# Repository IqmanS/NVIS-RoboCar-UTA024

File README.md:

## NVIS 3302ARD Robocar (UTA024: Engineering Design Project - II)
<p>
Read More about it: https://medium.com/@iqmans/creating-a-line-following-robocar-with-obstacle-detection-668964e0befc 
</p>
<p>
This is a Group Project and it is offered jointly by the department of Electronics Engineering and the department of Computer Engineering to the 2nd year students of all branches of Thapar Institute of Engineering and Technology.
</p>
<div align="center">
 
</div>

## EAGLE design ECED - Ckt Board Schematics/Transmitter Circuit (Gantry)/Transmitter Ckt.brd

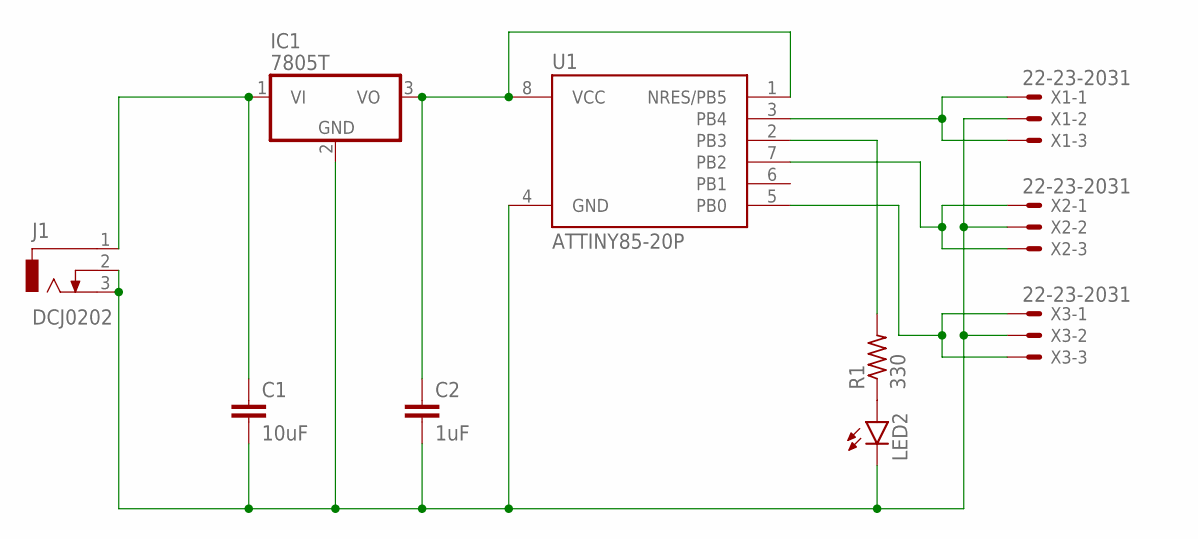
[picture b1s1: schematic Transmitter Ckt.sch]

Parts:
C1: 10uF; C0603
C2: 1uF; C0603
IC1: 7805T; TO220H
J1: DCJ0202
LED2: LED3MM
R1: 330; R0603
U1: ATTINY85-20P; PDIP08_300MIL
X1, X2, X3: 22-23-2031

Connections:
unnamed: LED2.A, R1.1
unnamed: C1.1, IC1.1 (VI), J1.1
unnamed: U1.3 (PB4), X1.1, X1.3
unnamed: C2.1, IC1.3 (VO), U1.1 (NRES/PB5), U1.8 (VCC)
unnamed: R1.2, U1.2 (PB3)
unnamed: U1.7 (PB2), X2.1, X2.3
unnamed: U1.5 (PB0), X3.1, X3.3
unnamed: C1.2, C2.2, IC1.2 (GND), J1.2, J1.3, LED2.K (C), U1.4 (GND), X1.2, X2.2, X3.2

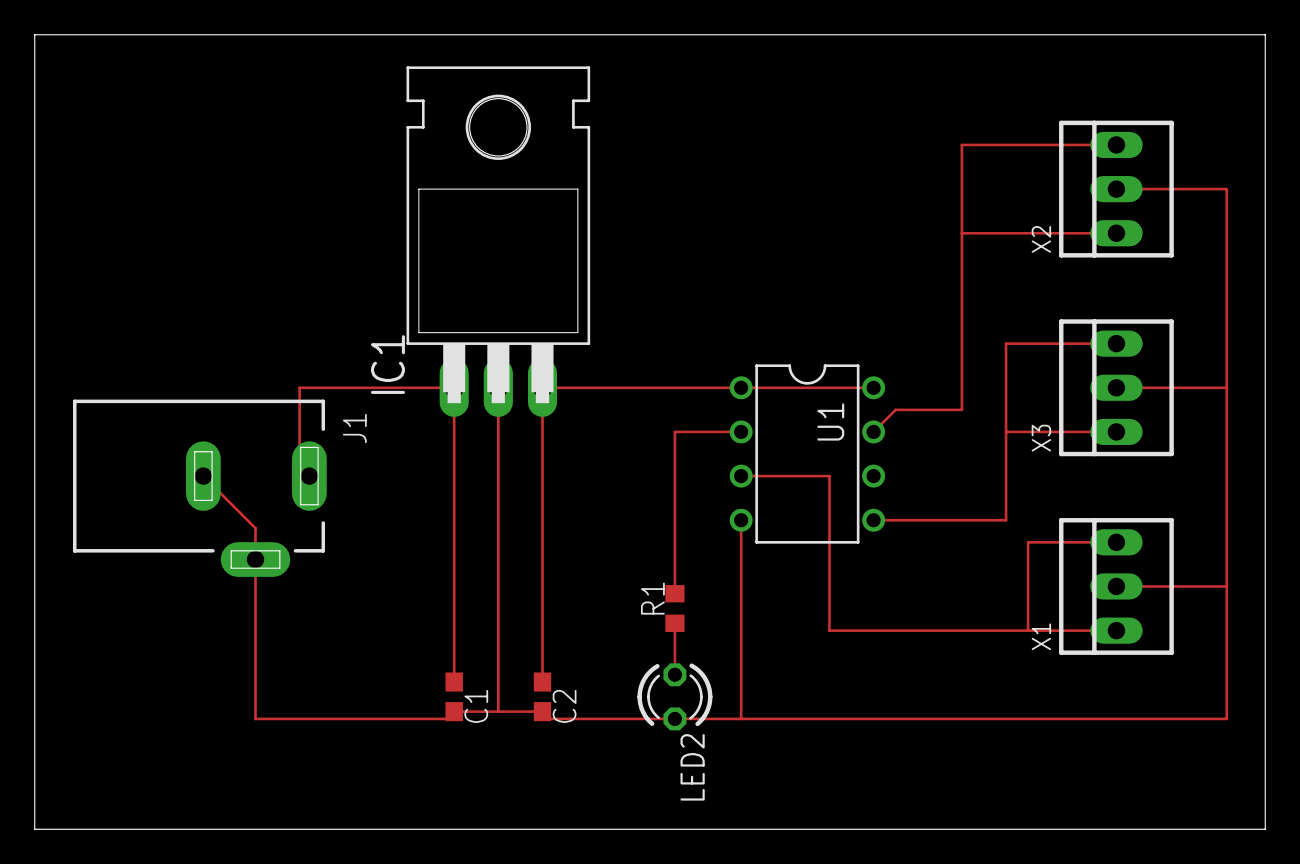
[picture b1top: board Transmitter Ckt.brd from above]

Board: 2 copper layers, 70.8 x 45.7 mm, 10 parts (0 on the bottom side), 8 nets.

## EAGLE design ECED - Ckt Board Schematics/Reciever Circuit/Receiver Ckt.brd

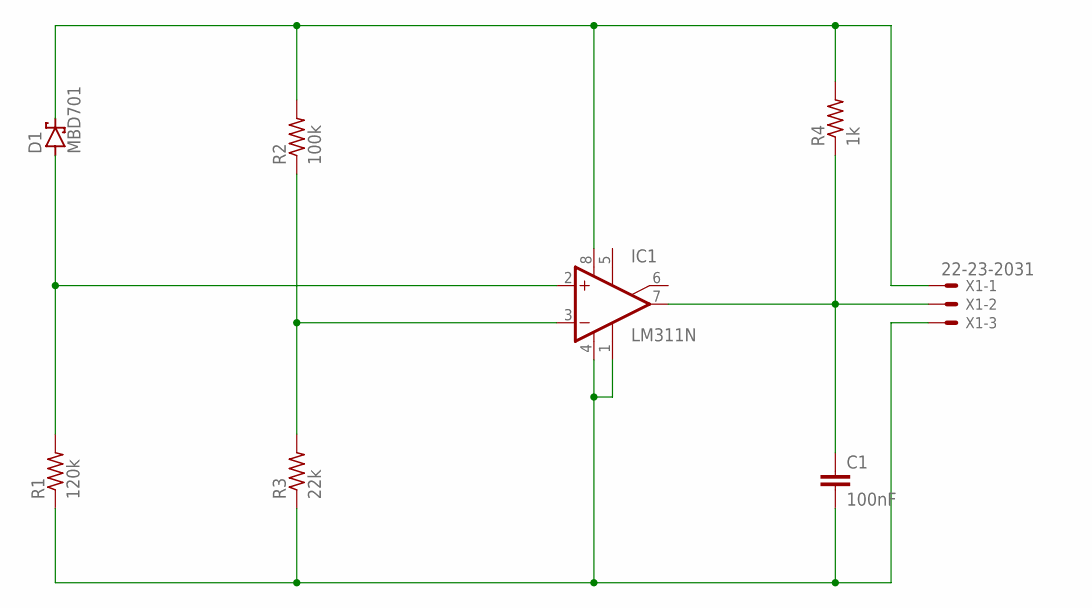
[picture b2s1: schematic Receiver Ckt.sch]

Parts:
C1: 100nF; C0603
D1: MBD701; TO92H
IC1: LM311N; DIL08
R1: 120k; R0603
R2: 100k; R0603
R3: 22k; R0603
R4: 1k; R0603
X1: 22-23-2031

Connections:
unnamed: D1.1 (A), IC1.2 (+IN), R1.2
unnamed: C1.2, IC1.1 (GND), IC1.4 (V-), R1.1, R3.1, X1.3
unnamed: D1.2 (C), IC1.8 (V+), R2.2, R4.2, X1.1
unnamed: C1.1, IC1.7 (OUT), R4.1, X1.2
unnamed: IC1.3 (-IN), R2.1, R3.2

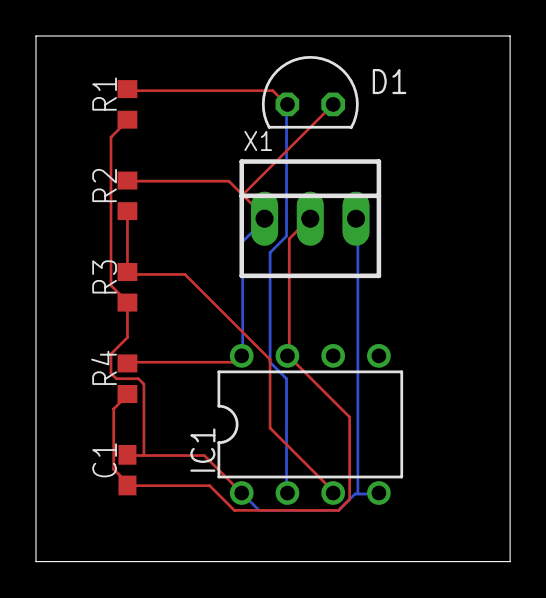
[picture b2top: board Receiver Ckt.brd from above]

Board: 2 copper layers, 26.3 x 29.2 mm, 8 parts (0 on the bottom side), 5 nets.

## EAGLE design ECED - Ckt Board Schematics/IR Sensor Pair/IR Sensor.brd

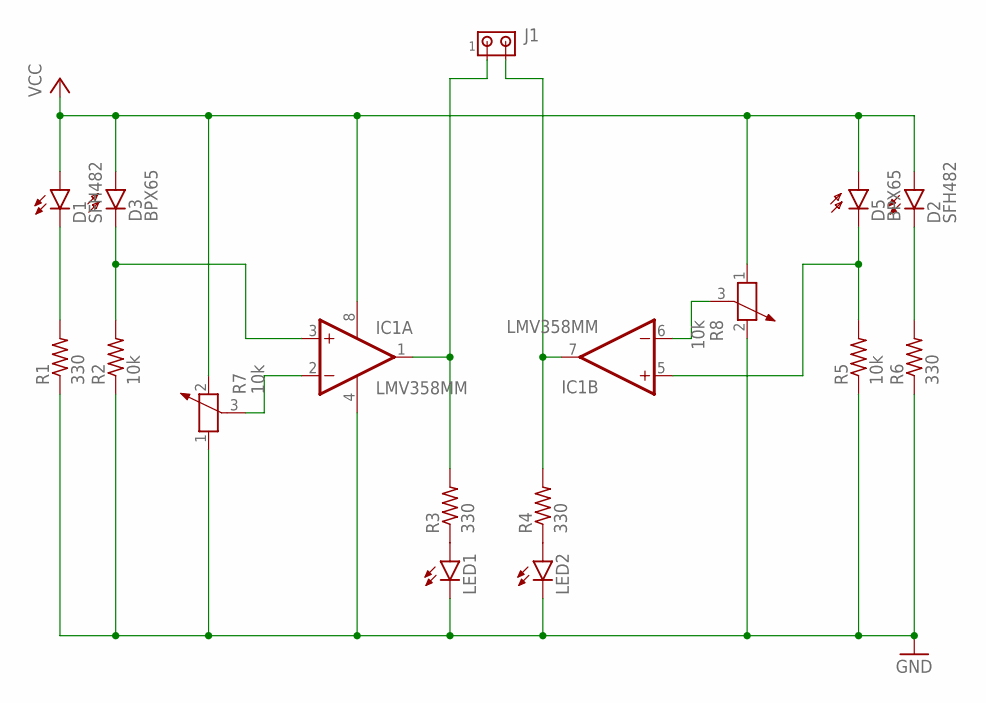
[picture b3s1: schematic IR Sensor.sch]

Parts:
D1, D2: SFH482
D3, D5: BPX65
IC1: LMV358MM; MSOP08
J1: MTA02-100; 10X02MTA
LED1, LED2: LED3MM
R1, R3, R4, R6: 330; R0603
R2, R5: 10k; R0603
R7, R8: 10k; PT-10

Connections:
GND: IC1.4 (V-), LED1.K (C), LED2.K (C), R1.1, R2.1, R5.1, R6.1, R7.1, R8.2
unnamed: LED1.A, R3.1
unnamed: LED2.A, R4.1
unnamed: D3.K (C), IC1.3 (+IN), R2.2
unnamed: D1.K (C), R1.2
unnamed: D2.K (C), R6.2
unnamed: D5.K (C), IC1.5 (+IN), R5.2
unnamed: IC1.2 (-IN), R7.3
unnamed: IC1.1 (OUT), J1.1, R3.2
unnamed: IC1.6 (-IN), R8.3
unnamed: IC1.7 (OUT), J1.2, R4.2
VCC: D1.A, D2.A, D3.A, D5.A, IC1.8 (V+), R7.2, R8.1

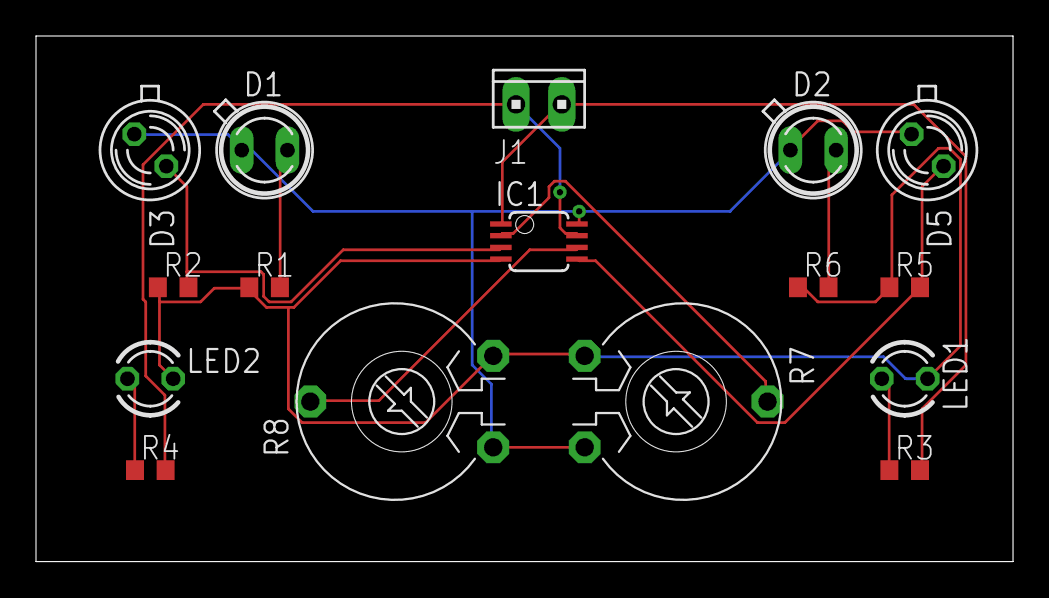
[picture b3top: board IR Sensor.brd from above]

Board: 2 copper layers, 54.3 x 29.2 mm, 16 parts (0 on the bottom side), 12 nets.

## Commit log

2023-04-30 Added Project Reports (CSED & ECED)
2023-05-04 Added Bronze Challenge
2023-05-04 Rename README.md to README.md
2023-05-04 Added Images of RoboCar on Track
2023-05-06 Added link to Medium article
